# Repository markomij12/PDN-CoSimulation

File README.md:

# PDN Co-Simulation

KiCad board in, decoupling BOM and impedance plots out.

I extract the power/ground cavity, run SPICE, and search a small catalog of real MLCCs (ESR/ESL, not ideal C) under a cost cap. Same loop SI/PI teams run with HFSS/SIwave and Cadence, minus the GUI.

A personal project exploring PCB power delivery network analysis with open-source tools.

```
boards/pdn_test.kicad_pcb
        │
        ├── openEMS (validator, run once) → results/board.s2p
        │
        └── fast cavity plane + discrete MLCC grid
                → BOM, via assignment, |Z(f)|, Pareto
                → optional 2-port ngspice check (all caps at port 2)
```

openEMS is how I check the mesh and ports. It is not inside `--optimize`. A 100 kHz–1 GHz PDN sweep is a bad FDTD problem, so the search uses a lumped cavity (plane C + spreading L to each VCC via). `--board` may run FDTD once when the layout changes; `--spice` and `--optimize` do not.

## How to run

After a clone (no openEMS required for `--optimize`; the coupon is already in `boards/`):

```bash
python3 -m venv .venv
source .venv/bin/activate
pip install -r requirements.txt
python run_pipeline.py                              # Phase 1 plate (analytical gate, not a PDN)
python run_pipeline.py --board boards/pdn_test.kicad_pcb
python run_pipeline.py --spice results/board.s2p
python run_pipeline.py --optimize results/board.s2p
pytest
```

`--board`, `--spice`, and `--optimize` are mutually exclusive.

macOS: `brew install ngspice`. The pipeline shells out to the `ngspice` binary; you do not need libngspice.

`--optimize` needs `boards/pdn_test.kicad_pcb`. If `results/board.s2p` or ngspice is missing, the plane search still runs and the 2-port check is skipped. If the board is missing, it errors.

Details per command are below. Package notes: `boards/README.md`, `spice_models/README.md`, `optimizer/README.md`.

### Phase 1 — `python run_pipeline.py`

This is a solver check, not a PDN. A real power/ground pair is wide and thin (Z0 ~ 1 Ω); S-parameters against 50 Ω are poorly conditioned, so I use a thicker, narrower plate (10 mm × 1.6 mm FR-4, Z0 ~ 28 Ω). PMC sidewalls, plates stop at the lumped ports.

Default run does not launch FDTD. `pytest` always checks closed-form Z0. When `results/parallel_plate.s2p` exists, |S| has to match the analytical line within 5% in the excite band (0.5–2.5 GHz). If that fails, the mesh or ports are wrong and there is no point continuing.

To regenerate the plate Touchstone (needs openEMS in the venv):

```bash
python -c "from pathlib import Path; from em_extraction import ParallelPlateGeometry; from em_extraction.openems_mesh import extract_sparams; extract_sparams(ParallelPlateGeometry.validation_plate(), sim_dir=Path('results/openems_parallel_plate'), output_s2p=Path('results/parallel_plate.s2p'))"
```

### Phase 2 — `--board boards/pdn_test.kicad_pcb`

Parses the `.kicad_pcb` as text (no `pcbnew`; that module only exists in KiCad's own Python). Reads vias, pads, and stackup, meshes the inner VCC/GND pair, writes `results/board.s2p` (gitignored). Port 1 is `U1` on `VCC`. Port 2 is a VCC via (`--decap-index N` to pick another).

Edit the board in KiCad, save, rerun. No hand-typed coordinates. `boards/README.md` has the net/footprint convention.

### Phase 3 — `--spice results/board.s2p`

Reads the cached `.s2p`, fits a lumped pi, runs ngspice. Does not refresh the Touchstone. If the file is missing, it tells you to run `--board` first.

Writes `results/droop.png`, `results/z_pdn.png`, and a short droop summary. VRM, MLCC RLC, and the pi fit: `spice_models/README.md`.

### Phase 4/5 — `--optimize results/board.s2p`

Inner loop is the plane plus a discrete grid: 0–3 of each of three Murata parts (64 stuffing vectors), assigned to the VCC vias on `pdn_test`. Score is peak |Z| from 100 kHz–30 MHz — that's the band where these MLCCs can still fight 50 mΩ. Plots still go to 1 GHz so you can see the 2 nH VRM / ESL climb. N ≤ 5 enumerates site assignments; more than that is greedy nearest-to-IC. No SciPy `minimize` on C. No openEMS.

The 2-port ngspice pass is a check of the winner with every MLCC at extracted port 2. It cannot see the other vias and it does not pick the BOM.

## Plots

`results/` is gitignored. Run `--optimize` and look under `results/`. GitHub shows the same filenames checked in under `docs/sample/`.

| File | What it is |
| --- | --- |
| `z_opt.png` | Plane Z(f): full band plus a 100 kHz–30 MHz zoom. Empty vs winner, 50 mΩ line, VRM |R+jωL|. |
| `pareto.png` | Peak Z in the search band vs BOM $ after placement. Feasible vs over budget, winner marked. |
| `z_spatial.png` | Search-band peak Z vs xy, IC and vias overlaid. |
| `bom_cost.txt` | Part, qty, unit $, total vs $0.50 budget. |
| `z_opt_2port.png`, `droop_opt.png` | 2-port check only (needs ngspice and `board.s2p`). |

`--spice` still writes `droop.png` and `z_pdn.png` from the `.s2p` alone.

## Sample run

A coupon `--optimize` is in `docs/sample/` — `cli.txt`, `bom_cost.txt`, and that folder's README. I'm not dumping every artifact here.

Empty vs winner on the plane. Search band is 100 kHz–30 MHz (354 mΩ → 43 mΩ, under 50 mΩ). The 1 GHz climb is the 2 nH VRM plus ESL — I'm not claiming I killed that.

Pareto of stuffing after placement, scored in that same band. Winner is one 100 nF 0402 + three 1 µF 0603 at $0.46.

Spatial map of search-band peak |Z|, U1 and the VCC vias marked.

## What this is not

The 2-port `.s2p` cannot move capacitors. Placement is on the plane; the SPICE check parks everything at port 2.

The plane is one cavity: parallel-plate C plus ln spreading L to each used via. Not a full cavity-mode series.

I did not hit 50 mΩ to 1 GHz, and I am not claiming I did. The search holds 50 mΩ through 30 MHz on this coupon. Default VRM `L_out` is 2 nH, so ωL is about 12.6 Ω at 1 GHz (1.26 Ω at 100 MHz). That climb is the inductor plus ESL, not “add another 22 µF”. The search constraint is BOM cost ($0.50). The 50 mΩ line is the same reference as `z_pdn.png`.

`pdn_test` is a 30 mm × 20 mm 4-layer coupon. VCC and GND sit on the inner pair with 0.2 mm dielectric (the PDN cavity). Two VCC vias are next to U1; one is farther out so placement still has a job.

## If I had more time

N-port extract so a SPICE check can see more than one via. VNA on a fabbed coupon vs the same `.s2p` / plane. A few more catalog SKUs, still discrete, still cost-capped. None of that is stubbed here.

## Stack

- Python 3.11+ (NumPy, SciPy, Matplotlib, pandas, pytest). PySpice is in `requirements.txt`; runtime is the `ngspice` binary.
- KiCad 8 for the coupon. Geometry comes from the s-expression, not `pcbnew`.
- openEMS / CSXCAD for the Phase 1 plate and Phase 2 `.s2p`.
- ngspice for Phase 3 and the optional optimizer check.

## FDTD install (only if you need `--board` or the plate `.s2p`)

Not pip. On the Mac I used: Homebrew `/opt/homebrew`, openEMS at `~/opt/openEMS`, bindings in this repo's `.venv`.

Rebuild from scratch on a new machine:

```bash
eval "$(/opt/homebrew/bin/brew shellenv)"
brew install cmake pkg-config boost hdf5 cgal vtk
git clone --recursive https://github.com/thliebig/openEMS-Project.git ~/src/openEMS-Project
python3.13 -m venv .venv
source .venv/bin/activate
pip install -U pip setuptools wheel cython
pip install -r requirements.txt h5py
export CMAKE_PREFIX_PATH="$(brew --prefix)"
cd ~/src/openEMS-Project
./update_openEMS.sh ~/opt/openEMS --python --disable-GUI
```

`--disable-GUI` skips AppCSXCAD (Qt). TinyXML comes with the script; Homebrew no longer ships it.

KiCad is optional if you only want to edit `boards/pdn_test.kicad_pcb`. `--spice` / `--optimize` do not need a rebuild of openEMS.

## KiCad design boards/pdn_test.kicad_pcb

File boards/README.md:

# Boards

Phase 1 is still the analytical plate in `em_extraction.geometry`, not a layout file.

Phase 2 board: `pdn_test.kicad_pcb` — a small 4-layer FR-4 coupon for the KiCad → openEMS bridge. You don't need the KiCad GUI; `read_board()` parses the s-expression in the project venv.

## `pdn_test.kicad_pcb`

| Item | Value |
| --- | --- |
| Size | 30 mm × 20 mm (`Edge.Cuts` rectangle at the origin) |
| Stackup | 1.6 mm FR-4-ish, 35 µm copper |
| F.Cu / B.Cu | signal (unused by the extractor) |
| In1.Cu | **VCC power plane** |
| In2.Cu | **GND plane** |
| Inner dielectric | 0.2 mm prepreg, εr = 4.5 (the PDN cavity, In1.Cu ↔ In2.Cu) |
| Core | 1.04 mm, εr = 4.5, F.Cu↔In1.Cu |
| Bottom prepreg | 0.2 mm, εr = 4.5, In2.Cu↔B.Cu |

The `.kicad_pcb` text file stores millimetres (KiCad's *internal* unit is nm). `em_extraction.kicad_reader.read_board` converts millimetres → metres in `BoardGeometry`.

## Net / footprint convention

`read_board()` identifies ports by **names**, not hardcoded xy:

| Role | How it is identified |
| --- | --- |
| Power net | `VCC` |
| Ground net | `GND` |
| IC power pin | footprint reference **`U1`**, pad on net `VCC` |
| Candidate decap sites | vias on net `VCC` |

`U1` is a dummy 2-pin load (pad 1 = VCC, pad 2 = GND). `C1` and `C2` sit next to U1; `C3` is farther out so the optimizer has a near/far placement choice. Move a VCC via in KiCad and re-run `python run_pipeline.py --board boards/pdn_test.kicad_pcb` to change the extracted S-parameters.

To add another decap candidate, place a via on net `VCC`. To move the IC pin, move footprint `U1`.

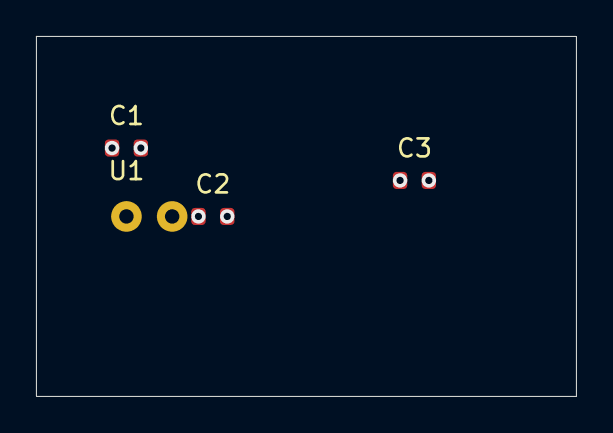
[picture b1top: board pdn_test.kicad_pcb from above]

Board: 4 copper layers, 30.0 x 20.0 mm, 4 parts (0 on the bottom side), 2 nets, no tracks yet.

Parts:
C1, C2, C3: C; C_0603_1608Metric
U1: LOAD; Load_2pin

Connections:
GND: C1.2, C2.2, C3.2, U1.2
VCC: C1.1, C2.1, C3.1, U1.1
